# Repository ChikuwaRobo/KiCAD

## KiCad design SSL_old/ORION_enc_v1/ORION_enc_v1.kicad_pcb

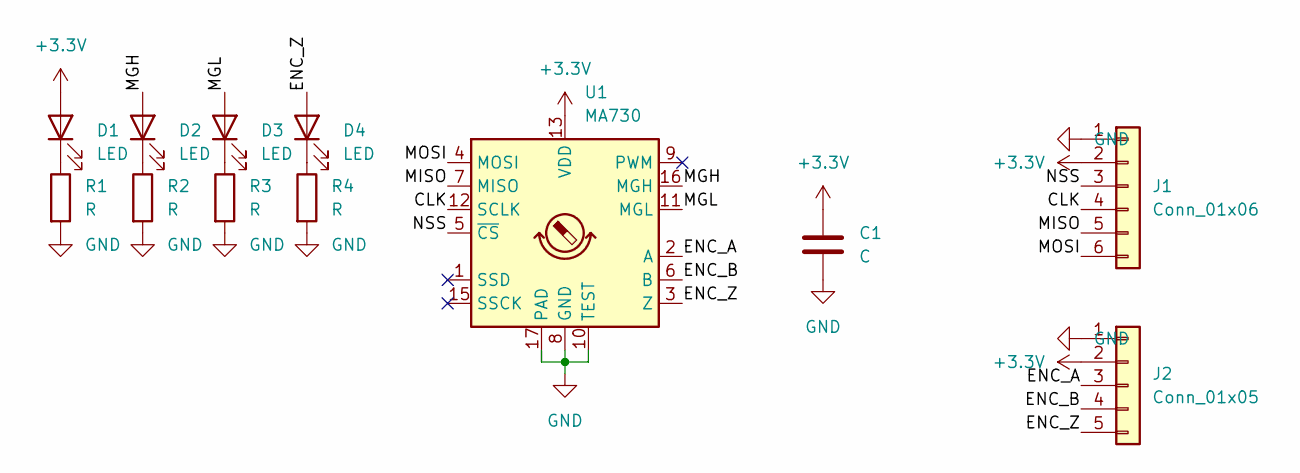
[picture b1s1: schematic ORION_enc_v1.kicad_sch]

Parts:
C1: C; C_0603_1608Metric
D1, D2, D3, D4: LED; LED_0603_1608Metric
J1: Conn_01x06; Hirose_DF13-06P-1.25DS_1x06_P1.25mm_Horizontal
J2: Conn_01x05; Hirose_DF13-05P-1.25DS_1x05_P1.25mm_Horizontal
R1, R2, R3, R4: R; R_0603_1608Metric
U1: MA730; QFN-16-1EP_3x3mm_P0.5mm_EP1.7x1.7mm

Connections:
+3V3: C1.1, D1.2 (A), J1.2, J2.2, U1.13 (VDD)
/CLK: J1.4, U1.12 (SCLK)
/ENC_A: J2.3, U1.2 (A)
/ENC_B: J2.4, U1.6 (B)
/ENC_Z: D4.2 (A), J2.5, U1.3 (Z)
/MGH: D2.2 (A), U1.16 (MGH)
/MGL: D3.2 (A), U1.11 (MGL)
/MISO: J1.5, U1.7 (MISO)
/MOSI: J1.6, U1.4 (MOSI)
/NSS: J1.3, U1.5 (~CS)
GND: C1.2, J1.1, J2.1, R1.2, R2.2, R3.2, R4.2, U1.8 (GND), U1.10 (TEST), U1.17 (PAD)
unnamed: D1.1 (K), R1.1
unnamed: D2.1 (K), R2.1
unnamed: D3.1 (K), R3.1
unnamed: D4.1 (K), R4.1

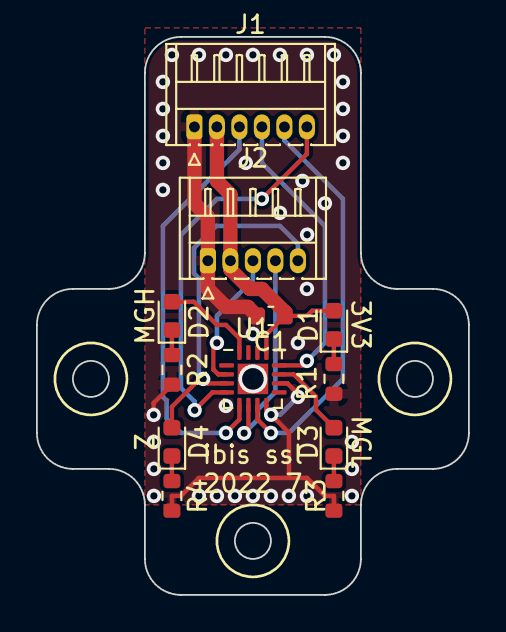
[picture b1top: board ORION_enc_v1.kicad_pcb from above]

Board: 2 copper layers, 24.0 x 31.0 mm, 12 parts (0 on the bottom side), 15 nets.

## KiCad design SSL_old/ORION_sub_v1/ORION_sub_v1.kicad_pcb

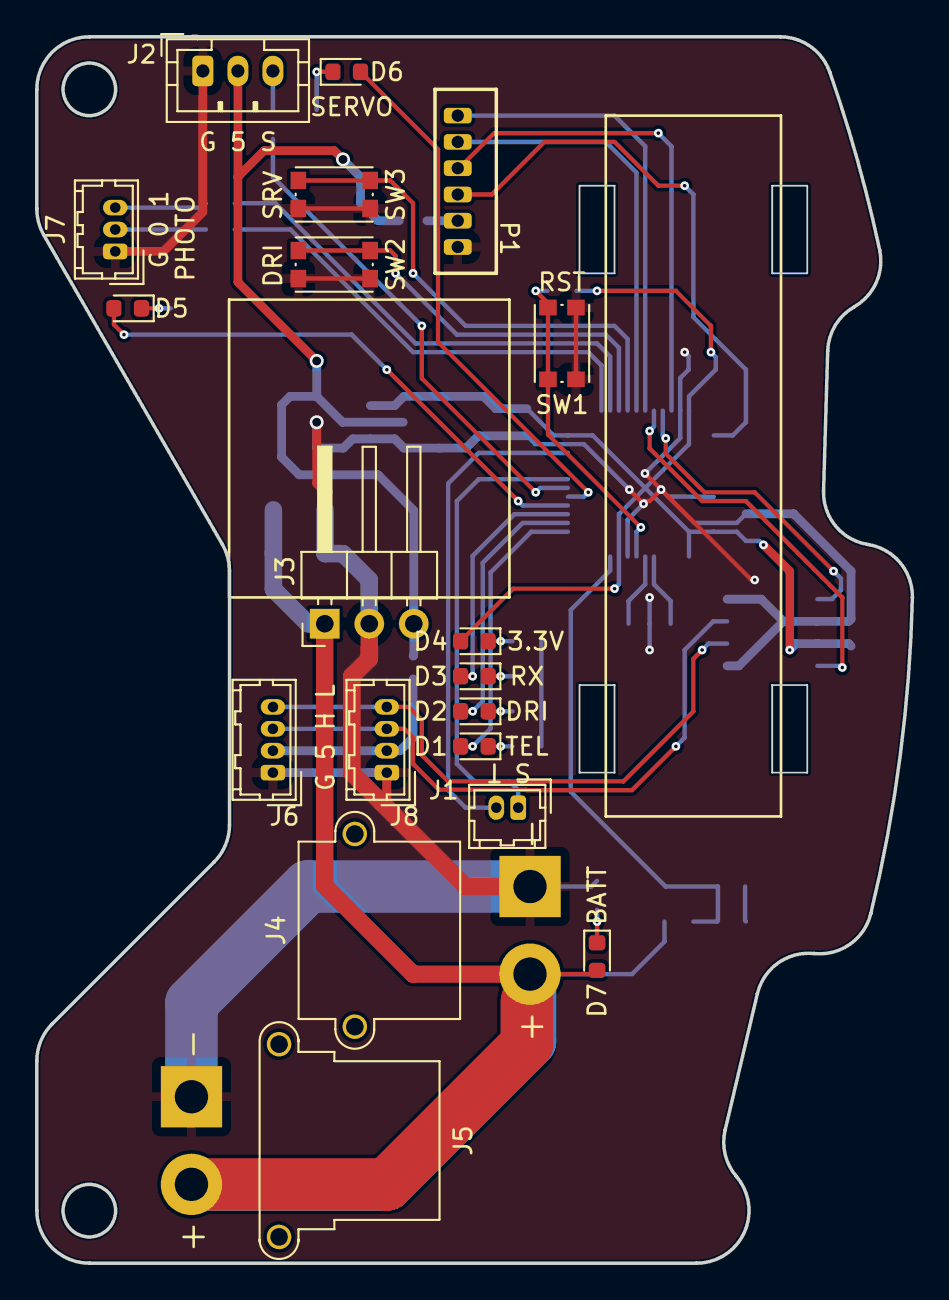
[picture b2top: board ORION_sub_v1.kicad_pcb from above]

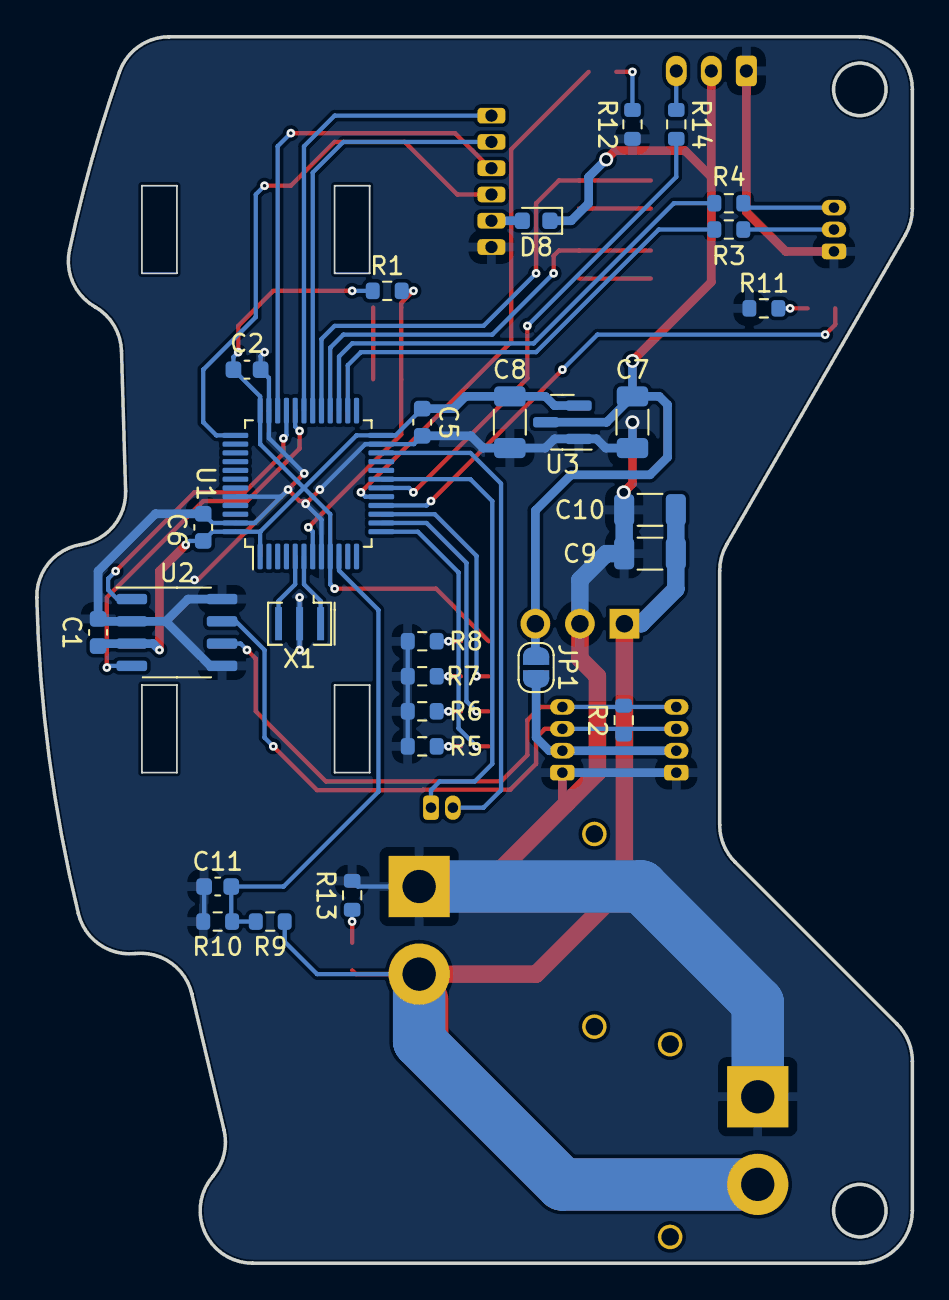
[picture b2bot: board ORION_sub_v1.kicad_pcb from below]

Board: 2 copper layers, 50.0 x 70.0 mm, 48 parts (29 on the bottom side), 40 nets.

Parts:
C1, C2, C5, C6, C11: 0.1u; C_0603_1608Metric
C7, C8, C9, C10: 4.7u; C_1206_3216Metric
D1, D2, D3, D4, D5, D6, D7: LED; LED_0603_1608Metric
D8: D; D_0603_1608Metric
J1: Conn_01x02; Hirose_DF13-02P-1.25DSA_1x02_P1.25mm_Vertical
J2: Conn_01x03; JST_PH_B3B-PH-K_1x03_P2.00mm_Vertical
J3: Conn_01x03; PinHeader_1x03_P2.54mm_Horizontal
J4: Conn_01x02; AMASS_XT30PW-M_1x02_P2.50mm_Horizontal
J5: Conn_01x02; AMASS_XT30PW-F_1x02_P2.50mm_Horizontal
J6, J8: Conn_01x04; Hirose_DF13-04P-1.25DSA_1x04_P1.25mm_Vertical
J7: Conn_01x03; Hirose_DF13-03P-1.25DSA_1x03_P1.25mm_Vertical
JP1: Jumper_2_Open; SolderJumper-2_P1.3mm_Open_RoundedPad1.0x1.5mm
P1: CONN_01X06; ZH_B6B-ZR
R1, R10: 1k; R_0603_1608Metric
R2: 120; R_0603_1608Metric
R3, R4, R14: 100; R_0603_1608Metric
R5, R6, R7, R8, R11, R12: 4.7k; R_0603_1608Metric
R9: 10k; R_0603_1608Metric
R13: 47k; R_0603_1608Metric
SW1, SW2, SW3: SW_Push; SW_Push_1P1T_NO_CK_KMR2
U1: STM32F303CBTx; LQFP-48_7x7mm_P0.5mm
U2: MAX3051; SO-8_3.9x4.9mm_P1.27mm
U3: AZ1117-3.3; SOT-23
X1: ceralock; Resonator_SMD_Murata_CSTxExxV-3Pin_3.0x1.1mm

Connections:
+3.3V: C1.2, C2.2, C5.2, C6.2, C8.1, D4.2 (A), R1.1, U1.1 (VBAT), U1.9 (VDDA), U1.24 (VDD), U1.36 (VDD), U1.48 (VDD), U2.3 (VDD), U3.2 (VO)
+5V: C7.1, D8.1 (K), J2.2, J3.3, JP1.1 (A), U3.3 (VI)
+BATT: C9.1, C10.1, D7.2 (A), J3.1, J4.2, J5.2, R9.1
/BATT_V: C11.2, R9.2, R10.1, U1.10 (PA0)
/CAN_H: J6.3, J8.3, R2.2, U2.7 (CANH)
/CAN_L: J6.4, J8.4, R2.1, U2.6 (CANL)
/CAN_RX: U1.32 (PA11), U2.4 (RXD)
/CAN_TX: U1.33 (PA12), U2.1 (TXD)
/ESC_PWM: J1.1, U1.19 (PB1)
/ESC_TLM: J1.2, U1.22 (PB11)
/LED_0: D1.2 (A), U1.13 (PA3)
/LED_1: D2.2 (A), U1.14 (PA4)
/LED_2: D3.2 (A), U1.15 (PA5)
/LED_3: D5.2 (A), U1.16 (PA6)
/LED_4: D6.2 (A), U1.17 (PA7)
/NRST: R1.2, SW1.1, U1.7 (NRST)
/OSC_IN: U1.5 (PF0), X1.3
/OSC_OUT: U1.6 (PF1), X1.1
/PHOTO_0: R3.2, U1.26 (PB13)
/PHOTO_1: R4.2, U1.27 (PB14)
/SERVO_PWM: R14.2, U1.18 (PB0)
/SWCLK: P1.3, U1.37 (PA14)
/SWDIO: P1.4, U1.34 (PA13)
/SW_0: SW2.2, U1.28 (PB15)
/SW_1: SW3.2, U1.29 (PA8)
/USART_RX: P1.6, U1.31 (PA10)
/USART_TX: P1.5, U1.30 (PA9)
GND: C1.1, C2.1, C5.1, C6.1, C7.2, C8.2, C9.2, C10.2, C11.1, J2.1, J3.2, J4.1, J5.1, J6.1, J7.1, J8.1, P1.1, R5.1, R6.1, R7.1, R8.1, R10.2, R11.1, R12.1, R13.1, SW1.2, SW2.1, SW3.1, U1.8 (VSSA), U1.23 (VSS), U1.35 (VSS), U1.44 (BOOT0), U1.47 (VSS), U2.2 (GND), U2.5 (SHDN), U2.8 (RS), U3.1 (GND), X1.2
unnamed: D1.1 (K), R5.2
unnamed: D2.1 (K), R6.2
unnamed: D3.1 (K), R7.2
unnamed: D4.1 (K), R8.2
unnamed: D5.1 (K), R11.2
unnamed: D6.1 (K), R12.2
unnamed: D7.1 (K), R13.2
unnamed: J2.3, R14.1
unnamed: J6.2, J8.2, JP1.2 (B)
unnamed: J7.2, R3.1
unnamed: J7.3, R4.1
unnamed: D8.2 (A), P1.2

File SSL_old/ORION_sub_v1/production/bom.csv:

Designator,Footprint,Quantity,Value,LCSC Part #
"C1, C11, C2, C5, C6",C_0603_1608Metric,5,0.1u,
"C10, C7, C8, C9",C_1206_3216Metric,4,4.7u,
"D1, D2, D3, D4, D5, D6, D7",LED_0603_1608Metric,7,LED,
D8,D_0603_1608Metric,1,D,
J1,Hirose_DF13-02P-1.25DSA_1x02_P1.25mm_Vertical,1,Conn_01x02,
J2,JST_PH_B3B-PH-K_1x03_P2.00mm_Vertical,1,Conn_01x03,
J3,PinHeader_1x03_P2.54mm_Horizontal,1,Conn_01x03,
J4,AMASS_XT30PW-M_1x02_P2.50mm_Horizontal,1,Conn_01x02,
J5,AMASS_XT30PW-F_1x02_P2.50mm_Horizontal,1,Conn_01x02,
"J6, J8",Hirose_DF13-04P-1.25DSA_1x04_P1.25mm_Vertical,2,Conn_01x04,
J7,Hirose_DF13-03P-1.25DSA_1x03_P1.25mm_Vertical,1,Conn_01x03,
JP1,SolderJumper-2_P1.3mm_Open_RoundedPad1.0x1.5mm,1,Jumper_2_Open,
P1,ZH_B6B-ZR,1,CONN_01X06,
"R1, R10",R_0603_1608Metric,2,1k,
"R11, R12, R5, R6, R7, R8",R_0603_1608Metric,6,4.7k,
R13,R_0603_1608Metric,1,47k,
"R14, R3, R4",R_0603_1608Metric,3,100,
R2,R_0603_1608Metric,1,120,
R9,R_0603_1608Metric,1,10k,
"SW1, SW2, SW3",SW_Push_1P1T_NO_CK_KMR2,3,SW_Push,
U1,LQFP-48_7x7mm_P0.5mm,1,STM32F303CBTx,
U2,SO-8_3.9x4.9mm_P1.27mm,1,MAX3051,
U3,SOT-23,1,AZ1117-3.3,
X1,Resonator_SMD_Murata_CSTxExxV-3Pin_3.0x1.1mm,1,ceralock,

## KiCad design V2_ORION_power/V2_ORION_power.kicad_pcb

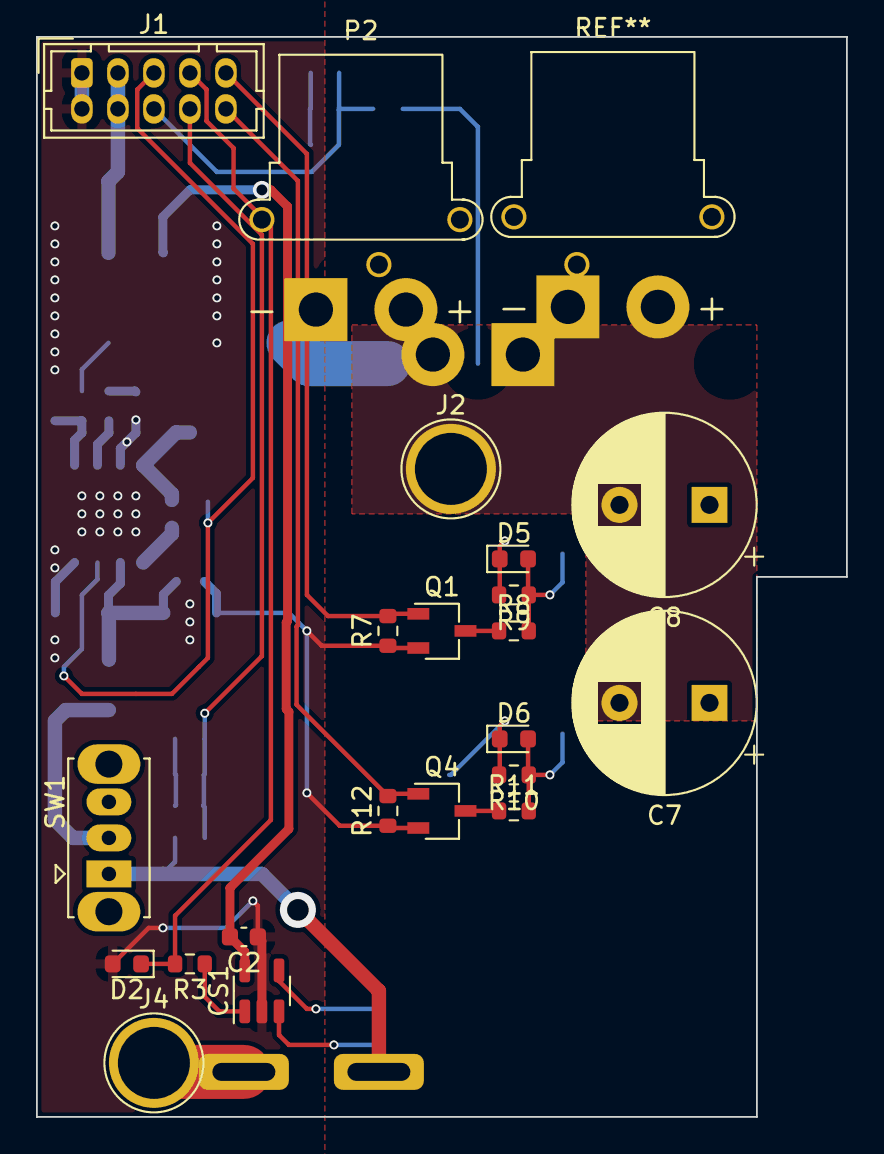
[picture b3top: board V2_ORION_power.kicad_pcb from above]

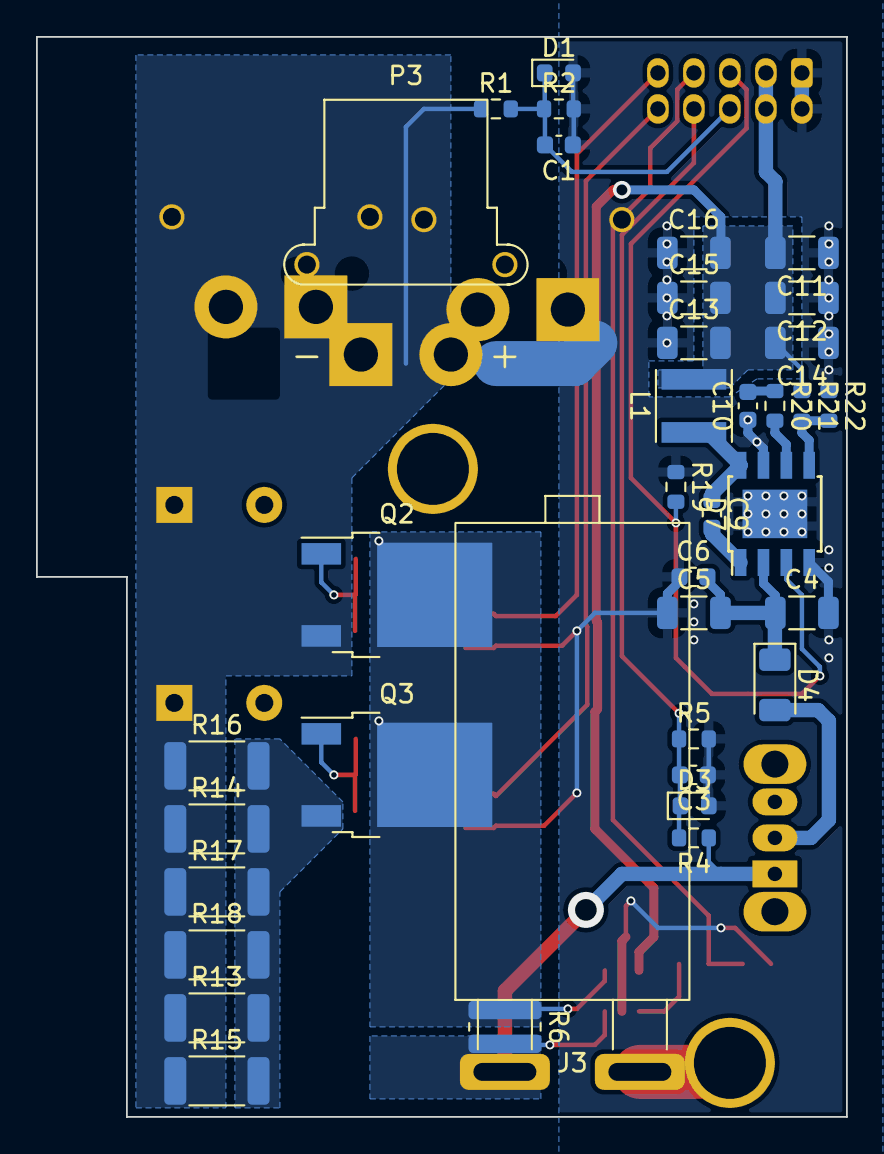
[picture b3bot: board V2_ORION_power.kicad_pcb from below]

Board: 2 copper layers, 45.0 x 60.0 mm, 58 parts (37 on the bottom side), 25 nets.

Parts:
C1, C2, C3, C6, C9: 0.1u; C_0603_1608Metric
C4, C5, C11, C12, C13, C14, C15, C16: 4.7u; C_1206_3216Metric
C7, C8: 470u; CP_Radial_D10.0mm_P5.00mm
C10: 1300p; C_0603_1608Metric
CS1: CS30; SOT-23-5
D1, D2, D3: D_Zener_3.3V; D_0603_1608Metric
D4: D; D_1206_3216Metric
D5, D6: D_Zener_12V; D_0603_1608Metric
D7: BD9E302EFJ; Diodes_PSOP-8
J1: Conn_02x05_Odd_Even; Hirose_DF11-10DP-2DSA_2x05_P2.00mm_Vertical
J2, J4: Conn_01x01; TestPoint_Plated_Hole_D4.0mm
J3: Conn_01x02; Reusable_Breaker
L1: 10uH; L_Vishay_IFSC-1515AH_4x4x1.8mm
P2, P3: CONN_01X02; AMASS_XT30PW-F_1x02_P2.50mm_Horizontal
Q1, Q4: Q_NMOS_GSD; TSOT-23
Q2, Q3: Q_PMOS_GDS; TO-252-2
R1, R4: 10k; R_0603_1608Metric
R2, R5, R7, R9, R10, R12, R19, R22: 1k; R_0603_1608Metric
R3, R8, R11: 100; R_0603_1608Metric
R6: 1m; R_0815_2038Metric
R13, R14, R15, R16, R17, R18: 1k; R_2010_5025Metric
R20: 6k; R_0603_1608Metric
R21: 15k; R_0603_1608Metric
SW1: SW_SPST_Temperature; SW_Slide_1P2T_CK_OS102011MS2Q

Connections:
+5V: C2.2, C11.2, C12.2, C13.2, C14.2, C15.2, C16.2, CS1.5 (VCC), J1.3, J1.4, L1.2, R21.1
+BATT: CS1.3 (Vp), J3.1, R4.1, R6.2, SW1.1 (A)
/BattVsense: C3.2, D3.1 (K), J1.8, R4.2, R5.1
/CurrentSense: D2.1 (K), J1.7, R3.2
/DCDC_5V_EN: D7.3 (EN), J1.5, R19.2
/PRE_CHARGE_EN: J1.10, Q4.1 (G), R12.2
/PW_OUT: C7.1, C8.1, P2.2, P3.2, Q2.3 (S), R1.1, R13.1, R14.1, R15.1, R16.1, R17.1, R18.1
/PW_OUT_EN: J1.9, Q1.1 (G), R7.2
/PowerOutVSense: C1.2, D1.1 (K), J1.6, R1.2, R2.1
GND: C1.1, C2.1, C3.1, C4.2, C5.1, C6.1, C7.2, C8.2, C10.1, C11.1, C12.1, C13.1, C14.1, C15.1, C16.1, CS1.2 (GND), D1.2 (A), D2.2 (A), D3.2 (A), D7.4 (AGND), D7.7 (PGND), D7.9 (PAD), J1.1, J1.2, J2.1, P2.1, P3.1, Q1.2 (S), Q4.2 (S), R2.2, R5.2, R7.1, R12.1, R19.1, R22.1
unnamed: C4.1, C5.2, C6.2, D4.1 (K), D7.2 (VIN)
unnamed: C9.1, D7.8 (SW), L1.1
unnamed: C9.2, D7.1 (BOOT)
unnamed: C10.2, R20.1
unnamed: CS1.1 (OUT), R3.1
unnamed: CS1.4 (Vm), D5.1 (K), D6.1 (K), Q2.2 (D), Q3.2 (D), R6.1, R9.2, R10.2
unnamed: D4.2 (A), SW1.2 (B)
unnamed: D5.2 (A), Q2.1 (G), R8.2, R9.1
unnamed: D6.2 (A), Q3.1 (G), R10.1, R11.2
unnamed: D7.5 (FB), R21.2, R22.2
unnamed: D7.6 (COMP), R20.2
unnamed: J3.2, J4.1
unnamed: Q1.3 (D), R8.1
unnamed: Q3.3 (S), R13.2, R14.2, R15.2, R16.2, R17.2, R18.2
unnamed: Q4.3 (D), R11.1

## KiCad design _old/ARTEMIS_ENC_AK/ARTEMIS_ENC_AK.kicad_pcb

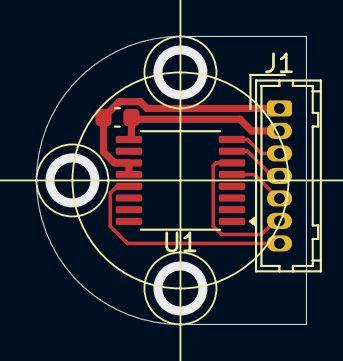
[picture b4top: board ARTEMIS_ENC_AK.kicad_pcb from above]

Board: 2 copper layers, 15.0 x 16.0 mm, 3 parts (0 on the bottom side), 7 nets.

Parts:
C1: C; C_0603_1608Metric
J1: Conn_01x07; Hirose_DF13-07P-1.25DSA_1x07_P1.25mm_Vertical
U1: AK7452; TSSOP-16_4.4x5mm_P0.65mm

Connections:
+3V3: C1.1, J1.2, U1.9 (VDD)
/ERROR: J1.7, U1.13 (ERROR)
/NSS_ENC: J1.3, U1.8 (~CSN)
/SPI_CLK: J1.4, U1.7 (SCLK)
/SPI_MISO: J1.5, U1.5 (MISO)
/SPI_MOSI: J1.6, U1.6 (MOSI)
GND: C1.2, J1.1, U1.11 (TESTE), U1.12 (VSS)

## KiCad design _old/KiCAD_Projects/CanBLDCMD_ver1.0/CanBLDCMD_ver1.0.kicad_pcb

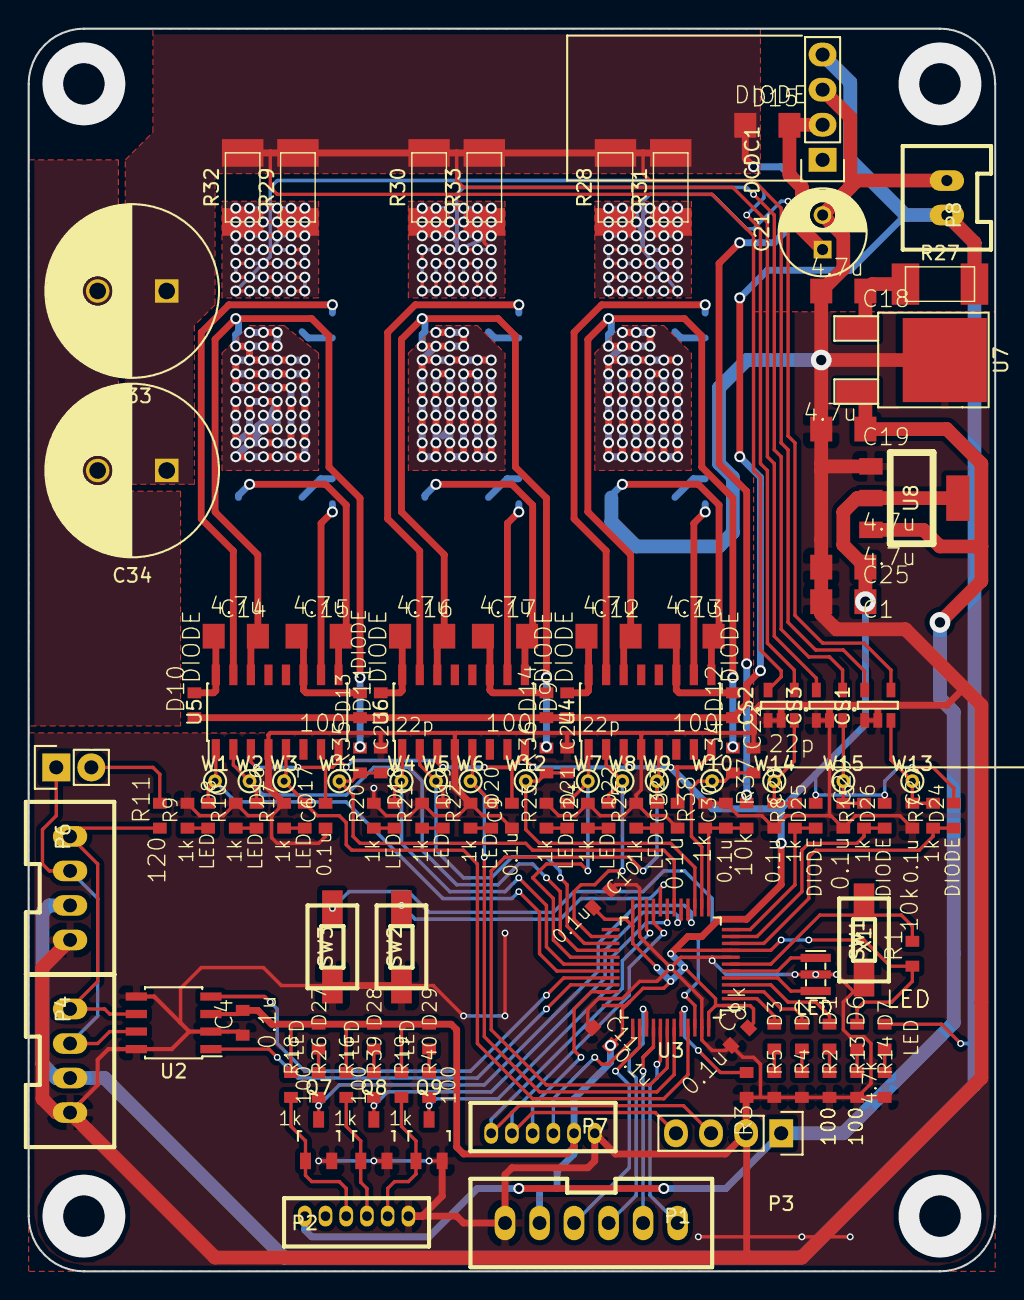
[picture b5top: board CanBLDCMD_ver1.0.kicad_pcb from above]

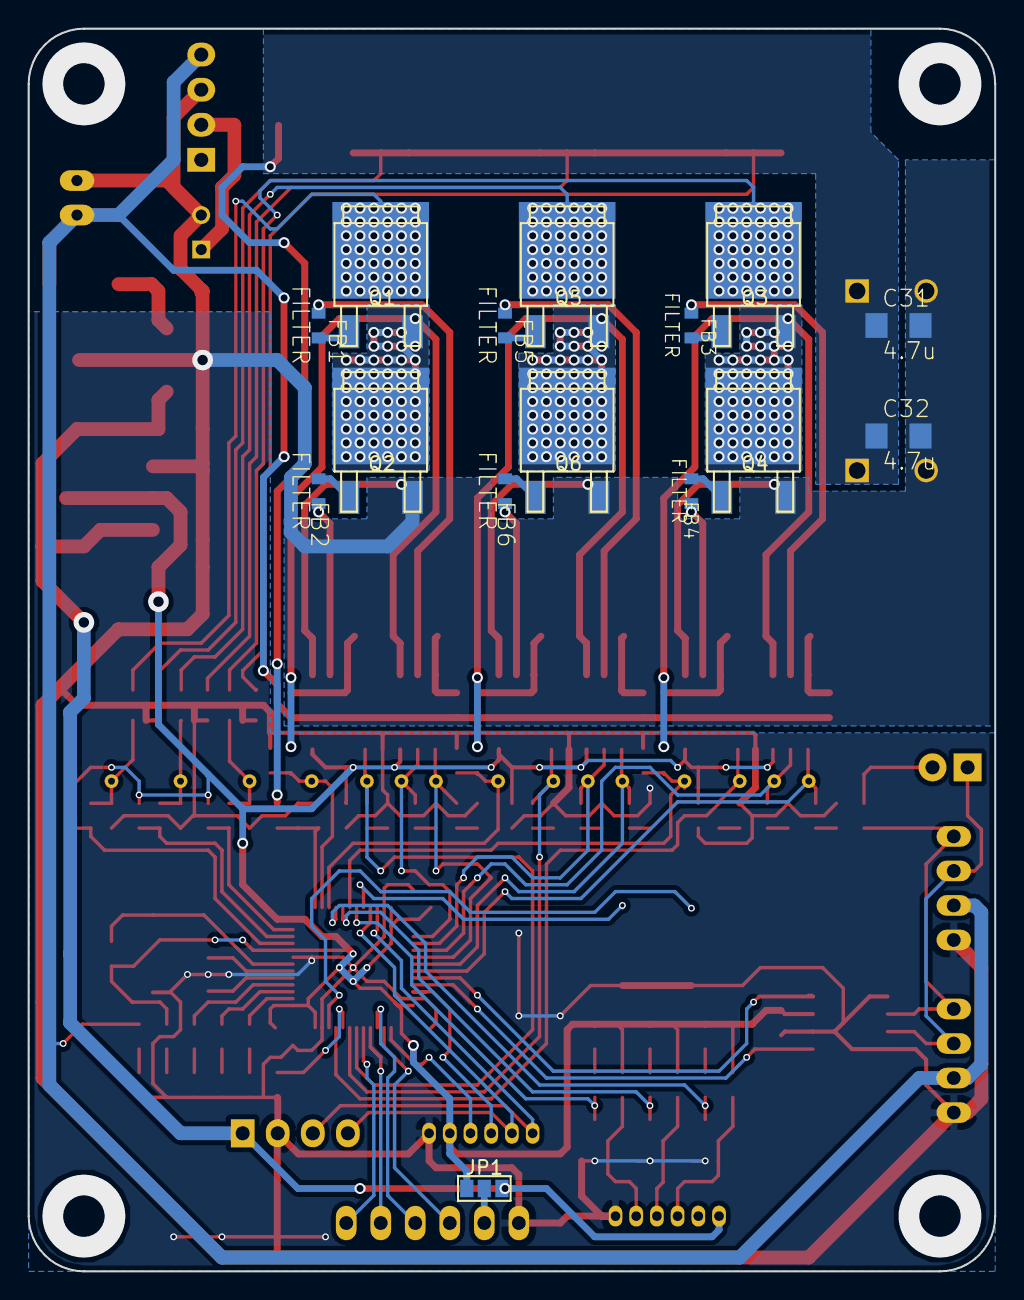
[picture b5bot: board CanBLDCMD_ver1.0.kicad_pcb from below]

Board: 2 copper layers, 70.0 x 90.0 mm, 148 parts (15 on the bottom side), 96 nets.

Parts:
C1, C12, C13, C14, C15, C16, C17, C18, C19, C25, C31, C32: 4.7u; C3216
C3, C4, C6, C8, C9, C10, C11, C27, C28, C29, C30: 0.1u; C1608_WP
C21: 100u; C_Radial_D6.3_L11.2_P2.5
C22, C23, C24: 22p; C1608_WP
C33, C34: 470u; C_Radial_D12.5_L25_P5
CS1, CS2, CS3: TS1102; SOT-23-5
D1, D2, D3, D6, D7, D8, D16, D17, D18, D19, D20, D21, D22, D23, D27, D28, D29: LED; C1608_WP
D9, D10, D11, D12, D13, D14, D24, D25, D26: DIODE; C1608_WP
D15: DIODE; C3216
DCDC1: ChinaDC-DC
FB1, FB2, FB3, FB4, FB5, FB6: FILTER; C1608_WP
JP1: JUMPER3; GS3
P1: CONN_01X06; XA_6T
P2, P7: CONN_01X06; ZH_6T
P3: CONN_01X04; Socket_Strip_Straight_1x04
P4, P6: CONN_01X04; XA_4T
P5: CONN_01X02; Pin_Header_Straight_1x02
P8: CONN_01X02; XA_2T
Q1, Q2, Q3, Q4, Q5, Q6: MOSFET_N; SOT-428_GDS_compact
Q7, Q8, Q9: MOSFET_N; SOT-23_Handsoldering
R1, R37: 10k; C1608_WP
R2, R4, R5, R13, R26, R34, R35, R36, R39, R40: 100; C1608_WP
R3, R7, R8, R9, R10, R15, R16, R17, R18, R19, R20, R21, R22, R23, R24, R25, R38: 1k; C1608_WP
R11: 120; C1608_WP
R14: 4.7k; C1608_WP
R27: 10; R5025
R28, R29, R30, R31, R32, R33: 1m; R5025
SW1, SW2, SW3: SW_PUSH; RP_SMD_Button
U2: MAX3051; SOIC-8_3.9x4.9mm_Pitch1.27mm
U3: STM32F103_48; LQFP-48_7x7mm_Pitch0.5mm
U4, U5, U6: SI8275; SOIC-16_3.9x9.9mm_Pitch1.27mm
U7: 7805; TO-252-2Lead_regu
U8: NCP1117ST33T3G; SOT-223_reg
W1, W2, W3, W4, W5, W6, W7, W8, W9, W10, W11, W12, W13, W14, W15: TEST_1P; PINTST
X1: ceralock; Resonator_3×1.3mm

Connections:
+3.3V: C1.1, C3.2, C4.2, C6.2, C8.2, C9.2, C10.2, C11.2, C25.1, D6.1, D24.2, D25.2, D26.2, D27.1, D28.1, D29.1, JP1.1, P7.2, R1.1, R16.1, R18.1, R19.1, U2.3, U3.1, U3.9, U3.24, U3.36, U3.48, U4.3, U4.8, U5.3, U5.8, U6.3, U6.8, U8.2
+5V: C19.1, JP1.3, P2.1, P3.1, U7.VO, U8.3
+12V: D7.1, D9.1, D10.1, D11.1, D12.1, D13.1, D14.1, DCDC1.4, P4.2, P6.2, P8.2, R27.2
+BATT: C31.1, C32.1, C33.1, C34.1, CS1.5, CS2.5, CS3.5, D15.1, R28.2, R29.2, R30.2, R31.2, R32.2, R33.2, R37.1
/BOOT0: R3.2, U3.44
/BattSense: C30.1, R37.2, R38.1, U3.13
/CANH: P4.3, P5.1, P6.3, U2.7
/CANL: P4.4, P6.4, R11.1, U2.6
/CAN_RX: U2.4, U3.32
/CAN_TX: U2.1, U3.33
/CS_U: D25.1, R8.1, U3.12
/CS_V: D26.1, R15.1, U3.11
/CS_W: D24.1, R7.1, U3.10
/EN_U: D17.1, U3.45, U5.5, W3.1
/EN_V: D20.1, U3.43, U6.5, W6.1
/EN_W: D23.1, U3.42, U4.5, W9.1
/HALL_0: Q7.D, R26.2, U3.16
/HALL_1: Q8.D, R39.2, U3.17
/HALL_2: Q9.D, R40.2, U3.19
/LED_C: D3.1, U3.2
/LED_D: D2.1, U3.3
/LED_E: D1.1, U3.4
/NRST: R1.2, SW1.2, U3.7
/OSC_IN: U3.5, X1.3
/OSC_OUT: U3.6, X1.1
/OUT_U: C14.2, Q3.S, Q4.D, R35.2, U5.14
/OUT_V: C16.2, Q5.S, Q6.D, R36.2, U6.14
/OUT_W: C12.2, Q1.S, Q2.D, R34.2, U4.14
/PWM_U_H: D8.1, U3.31, U5.1, W1.1
/PWM_U_L: D16.1, U3.28, U5.2, W2.1
/PWM_V_H: D18.1, U3.30, U6.1, W4.1
/PWM_V_L: D19.1, U3.27, U6.2, W5.1
/PWM_W_H: D21.1, U3.29, U4.1, W7.1
/PWM_W_L: D22.1, U3.26, U4.2, W8.1
/SPI_MISO: P1.5, U3.40
/SPI_MOSI: P1.6, U3.41
/SPI_NSS: P1.3, U3.38
/SPI_SCK: P1.4, U3.39
/SW1: SW2.2, U3.20
/SW2: SW3.2, U3.46
/SWCLK: P7.3, U3.37
/SWDIO: P7.4, U3.34
/USART_RX: P3.3, P7.6, U3.22
/USART_TX: P3.4, P7.5, U3.21
/Vsense_U: C23.2, R35.1, U3.18, W11.1
/Vsense_V: C24.2, R36.1, U3.15, W12.1
/Vsense_W: C22.2, R34.1, U3.14, W10.1
GND: C1.2, C3.1, C4.1, C6.1, C8.1, C9.1, C10.1, C11.1, C13.2, C15.2, C17.2, C18.2, C19.2, C21.2, C22.1, C23.1, C24.1, C25.2, C27.2, C28.2, C29.2, C30.2, C31.2, C32.2, C33.2, C34.2, CS1.1, CS1.2, CS2.1, CS2.2, CS3.1, CS3.2, DCDC1.3, P1.1, P2.6, P3.2, P4.1, P6.1, P7.1, P8.1, Q2.S, Q4.S, Q6.S, Q7.S, Q8.S, Q9.S, R2.2, R3.1, R4.2, R5.2, R9.2, R10.2, R13.2, R14.2, R17.2, R20.2, R21.2, R22.2, R23.2, R24.2, R25.2, R38.2, SW1.1, SW2.1, SW3.1, U2.2, U2.5, U2.8, U3.8, U3.23, U3.35, U3.47, U4.4, U4.9, U5.4, U5.9, U6.4, U6.9, U7.GND, U8.1, X1.2
unnamed: C12.1, D9.2, U4.16
unnamed: C13.1, D12.2, U4.11
unnamed: C14.1, D10.2, U5.16
unnamed: C15.1, D13.2, U5.11
unnamed: C16.1, D11.2, U6.16
unnamed: C17.1, D14.2, U6.11
unnamed: C18.1, R27.1, U7.VI
unnamed: C21.1, D15.2, DCDC1.2
unnamed: C27.1, CS1.3, R7.2, W13.1
unnamed: C28.1, CS2.3, R8.2, W14.1
unnamed: C29.1, CS3.3, R15.2, W15.1
unnamed: CS1.4, Q1.D, R28.1, R31.1
unnamed: CS2.4, Q3.D, R29.1, R32.1
unnamed: CS3.4, Q5.D, R30.1, R33.1
unnamed: D1.2, R2.1
unnamed: D2.2, R4.1
unnamed: D3.2, R5.1
unnamed: D6.2, R13.1
unnamed: D7.2, R14.1
unnamed: D8.2, R9.1
unnamed: D16.2, R10.1
unnamed: D17.2, R17.1
unnamed: D18.2, R20.1
unnamed: D19.2, R21.1
unnamed: D20.2, R22.1
unnamed: D21.2, R23.1
unnamed: D22.2, R24.1
unnamed: D23.2, R25.1
unnamed: D27.2, R26.1
unnamed: D28.2, R39.1
unnamed: D29.2, R40.1
unnamed: FB1.1, U4.15
unnamed: FB1.2, Q1.G
unnamed: FB2.1, U4.10
unnamed: FB2.2, Q2.G
unnamed: FB3.1, U5.15
unnamed: FB3.2, Q3.G
unnamed: FB4.1, U5.10
unnamed: FB4.2, Q4.G
unnamed: FB5.1, U6.15
unnamed: FB5.2, Q5.G
unnamed: FB6.1, U6.10
unnamed: FB6.2, Q6.G
unnamed: JP1.2, P1.2
unnamed: P2.3, Q7.G, R18.2
unnamed: P2.4, Q8.G, R16.2
unnamed: P2.5, Q9.G, R19.2
unnamed: P5.2, R11.2

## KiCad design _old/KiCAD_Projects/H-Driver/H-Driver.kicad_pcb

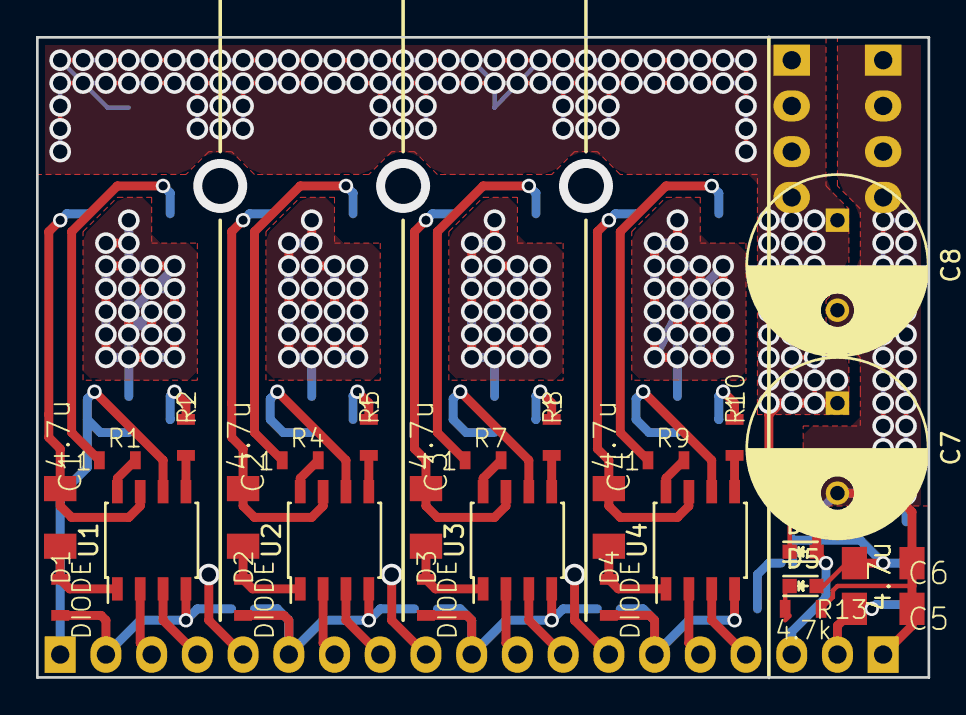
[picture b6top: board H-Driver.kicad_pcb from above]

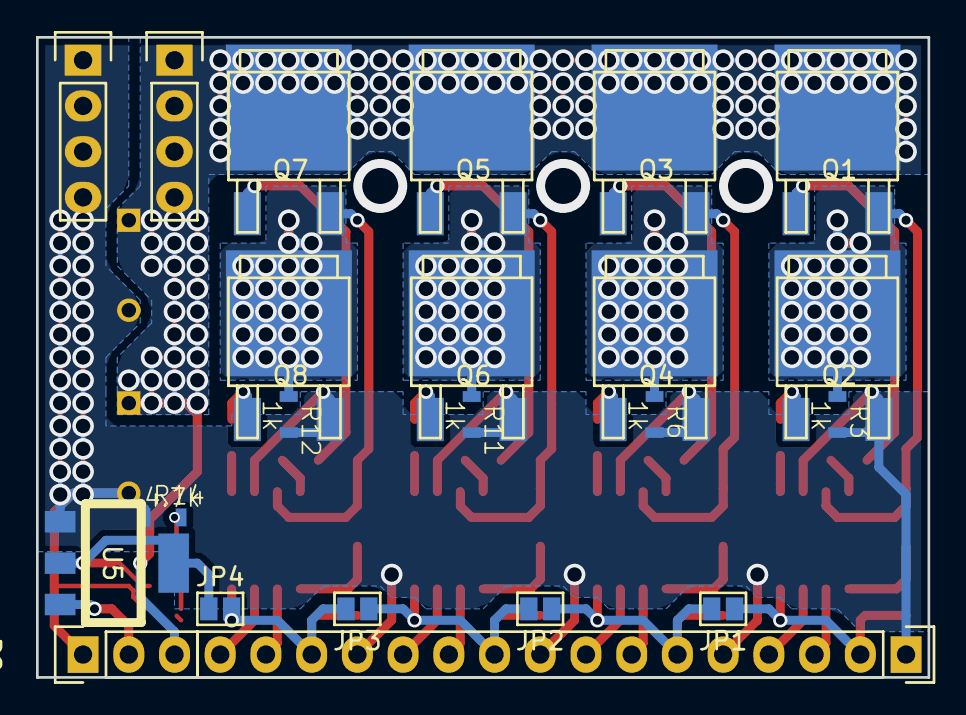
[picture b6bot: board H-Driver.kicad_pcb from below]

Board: 2 copper layers, 49.5 x 35.6 mm, 49 parts (22 on the bottom side), 42 nets.

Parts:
C1, C2, C3, C4, C5, C6: 4.7u; C3216_S
C7, C8: 470u; C_Radial_D10_L13_P5
D1, D2, D3, D4: DIODE; C1608_WP_S
D5, D6: LED; LED_0603
JP1, JP2, JP3, JP4: JUMPER; GS2
P1: CONN_01X16; Pin_Header_Straight_1x16
P2: CONN_01X03; Pin_Header_Straight_1x03
P3, P4: CONN_01X04; Pin_Header_Straight_1x04
Q1, Q2, Q3, Q4, Q5, Q6, Q7, Q8: MOSFET_N; SOT-428_GDS_compact
R1, R2, R4, R5, R7, R8, R9, R10: 1; C1608_WP_S
R3, R6, R11, R12: 1k; C1608_WP_S
R13, R14: 4.7k; C1608_WP_S
U1, U2, U3, U4: NCP5359; SOIC-8_3.9x4.9mm_Pitch1.27mm_S
U5: NCP1117ST12T3G; SOT-223_reg

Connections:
+12V: C6.2, D5.1, JP4.1, U5.2
+BATT: C7.1, C8.1, D6.1, P2.3, P3.1, P3.2, P3.3, P3.4, Q1.D, Q3.D, Q5.D, Q7.D
/BST_0: D1.2, JP1.1, P1.2, U1.4
/BST_1: D2.2, JP1.2, JP2.1, P1.6, U2.4
/BST_2: D3.2, JP2.2, JP3.1, P1.10, U3.4
/BST_3: D4.2, JP3.2, JP4.2, P1.14, U4.4
/EN_0: P1.4, U1.3
/EN_1: P1.8, U2.3
/EN_2: P1.12, U3.3
/EN_3: P1.16, U4.3
/OUT_0: C1.1, Q1.S, Q2.D, R3.1, U1.7
/OUT_1: C2.1, Q3.S, Q4.D, R6.1, U2.7
/OUT_2: C3.1, Q5.S, Q6.D, R11.1, U3.7
/OUT_3: C4.1, Q7.S, Q8.D, R12.1, U4.7
/PWM_0: P1.3, U1.2
/PWM_1: P1.7, U2.2
/PWM_2: P1.11, U3.2
/PWM_3: P1.15, U4.2
/regBatt: C5.2, P2.2, U5.3
GND: C5.1, C6.1, C7.2, C8.2, P1.1, P1.5, P1.9, P1.13, P2.1, P4.1, P4.2, P4.3, P4.4, Q2.S, Q4.S, Q6.S, Q8.S, R3.2, R6.2, R11.2, R12.2, R13.1, R14.1, U1.6, U2.6, U3.6, U4.6, U5.1
unnamed: C1.2, D1.1, U1.1
unnamed: C2.2, D2.1, U2.1
unnamed: C3.2, D3.1, U3.1
unnamed: C4.2, D4.1, U4.1
unnamed: D5.2, R13.2
unnamed: D6.2, R14.2
unnamed: Q1.G, R1.1
unnamed: Q2.G, R2.1
unnamed: Q3.G, R4.1
unnamed: Q4.G, R5.1
unnamed: Q5.G, R7.1
unnamed: Q6.G, R8.1
unnamed: Q7.G, R9.1
unnamed: Q8.G, R10.1
unnamed: R1.2, U1.8
unnamed: R2.2, U1.5
unnamed: R4.2, U2.8
unnamed: R5.2, U2.5
unnamed: R7.2, U3.8
unnamed: R8.2, U3.5
unnamed: R9.2, U4.8
unnamed: R10.2, U4.5
